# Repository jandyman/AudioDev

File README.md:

# AudioDev

Audio DSP development ecosystem for algorithm development, testing, and deployment.

## Active Projects

### [audio-graph-python](./audio-graph-python/)
Hybrid Faust/C++ audio processing graph system with Python control.
- Flat channel model (all signals mono, multichannel = N parallel signals)
- Uniform interface for Faust and C++ processors
- Named processor access, capture mode for debugging, chunked processing
- Graph specification language for cascade definitions

### [dsp_library](./dsp_library/)
Framework-agnostic C++ and Faust DSP implementations shared across platforms.
- **C++ Processors**: example_processor, split_chorus
- **Faust Modules**: gain, split_gain, dual_tap_delay (9th order Lagrange interpolation)
- Single source of truth: write DSP once, wrap for Python and Max

### [max_externals](./max_externals/)
Max/MSP external wrappers for DSP processors.
- **dual_tap_delay~**: Faust-based dual tap delay
- **split_chorus~**: C++ split chorus effect
- Thin wrappers that include DSP from dsp_library

## Reference Projects

### [Embedded DSP DevSystem](./Embedded%20DSP%20DevSystem/)
Conceptual framework for DSP algorithm development lifecycle (Python prototyping to embedded C++).
Contains design documents and architectural decisions.

### [DaisyExamples](./DaisyExamples/)
Examples for Electro-Smith Daisy embedded audio platform. 80+ DSP algorithm examples.

### [SciPy](./SciPy/)
Python-based signal processing algorithm development and analysis.

### [PitchShifter](./PitchShifter/)
Early-stage bass guitar pitch shifter concept.

## Architecture

```
AudioDev/
├── dsp_library/           # Core DSP implementations (C++ and Faust)
│   ├── cpp/               # Framework-agnostic C++ DSP
│   └── faust/             # Faust DSP modules
├── audio-graph-python/    # Python graph system + pybind11 bindings
│   ├── python/            # Graph system
│   ├── bindings/          # pybind11 wrappers for dsp_library
│   └── examples/          # Working examples
├── max_externals/         # Max/MSP external wrappers
│   ├── dual_tap_delay_tilde/
│   └── split_chorus_tilde/
└── ...                    # Reference projects
```

## Design Principles

1. **Single source of truth**: DSP code lives in `dsp_library/`, wrapped for each platform
2. **Flat channel model**: All signals are mono, multichannel is N parallel mono signals
3. **Uniform interface**: All processors expose `init/process/set_param/get_param`
4. **Framework-agnostic**: Core DSP has no dependencies on Max, Python, or any framework

## Getting Started

See [audio-graph-python/QUICKSTART.md](./audio-graph-python/QUICKSTART.md) for a 5-minute introduction.

## Recent Changes

See [audio-graph-python/CHANGELOG.md](./audio-graph-python/CHANGELOG.md) for recent updates.

**Latest (2026-01-15)**:
- Split chorus C++ module with Python bindings
- Graph specification language for cascade definitions
- File reorganization with dsp_library as central DSP source

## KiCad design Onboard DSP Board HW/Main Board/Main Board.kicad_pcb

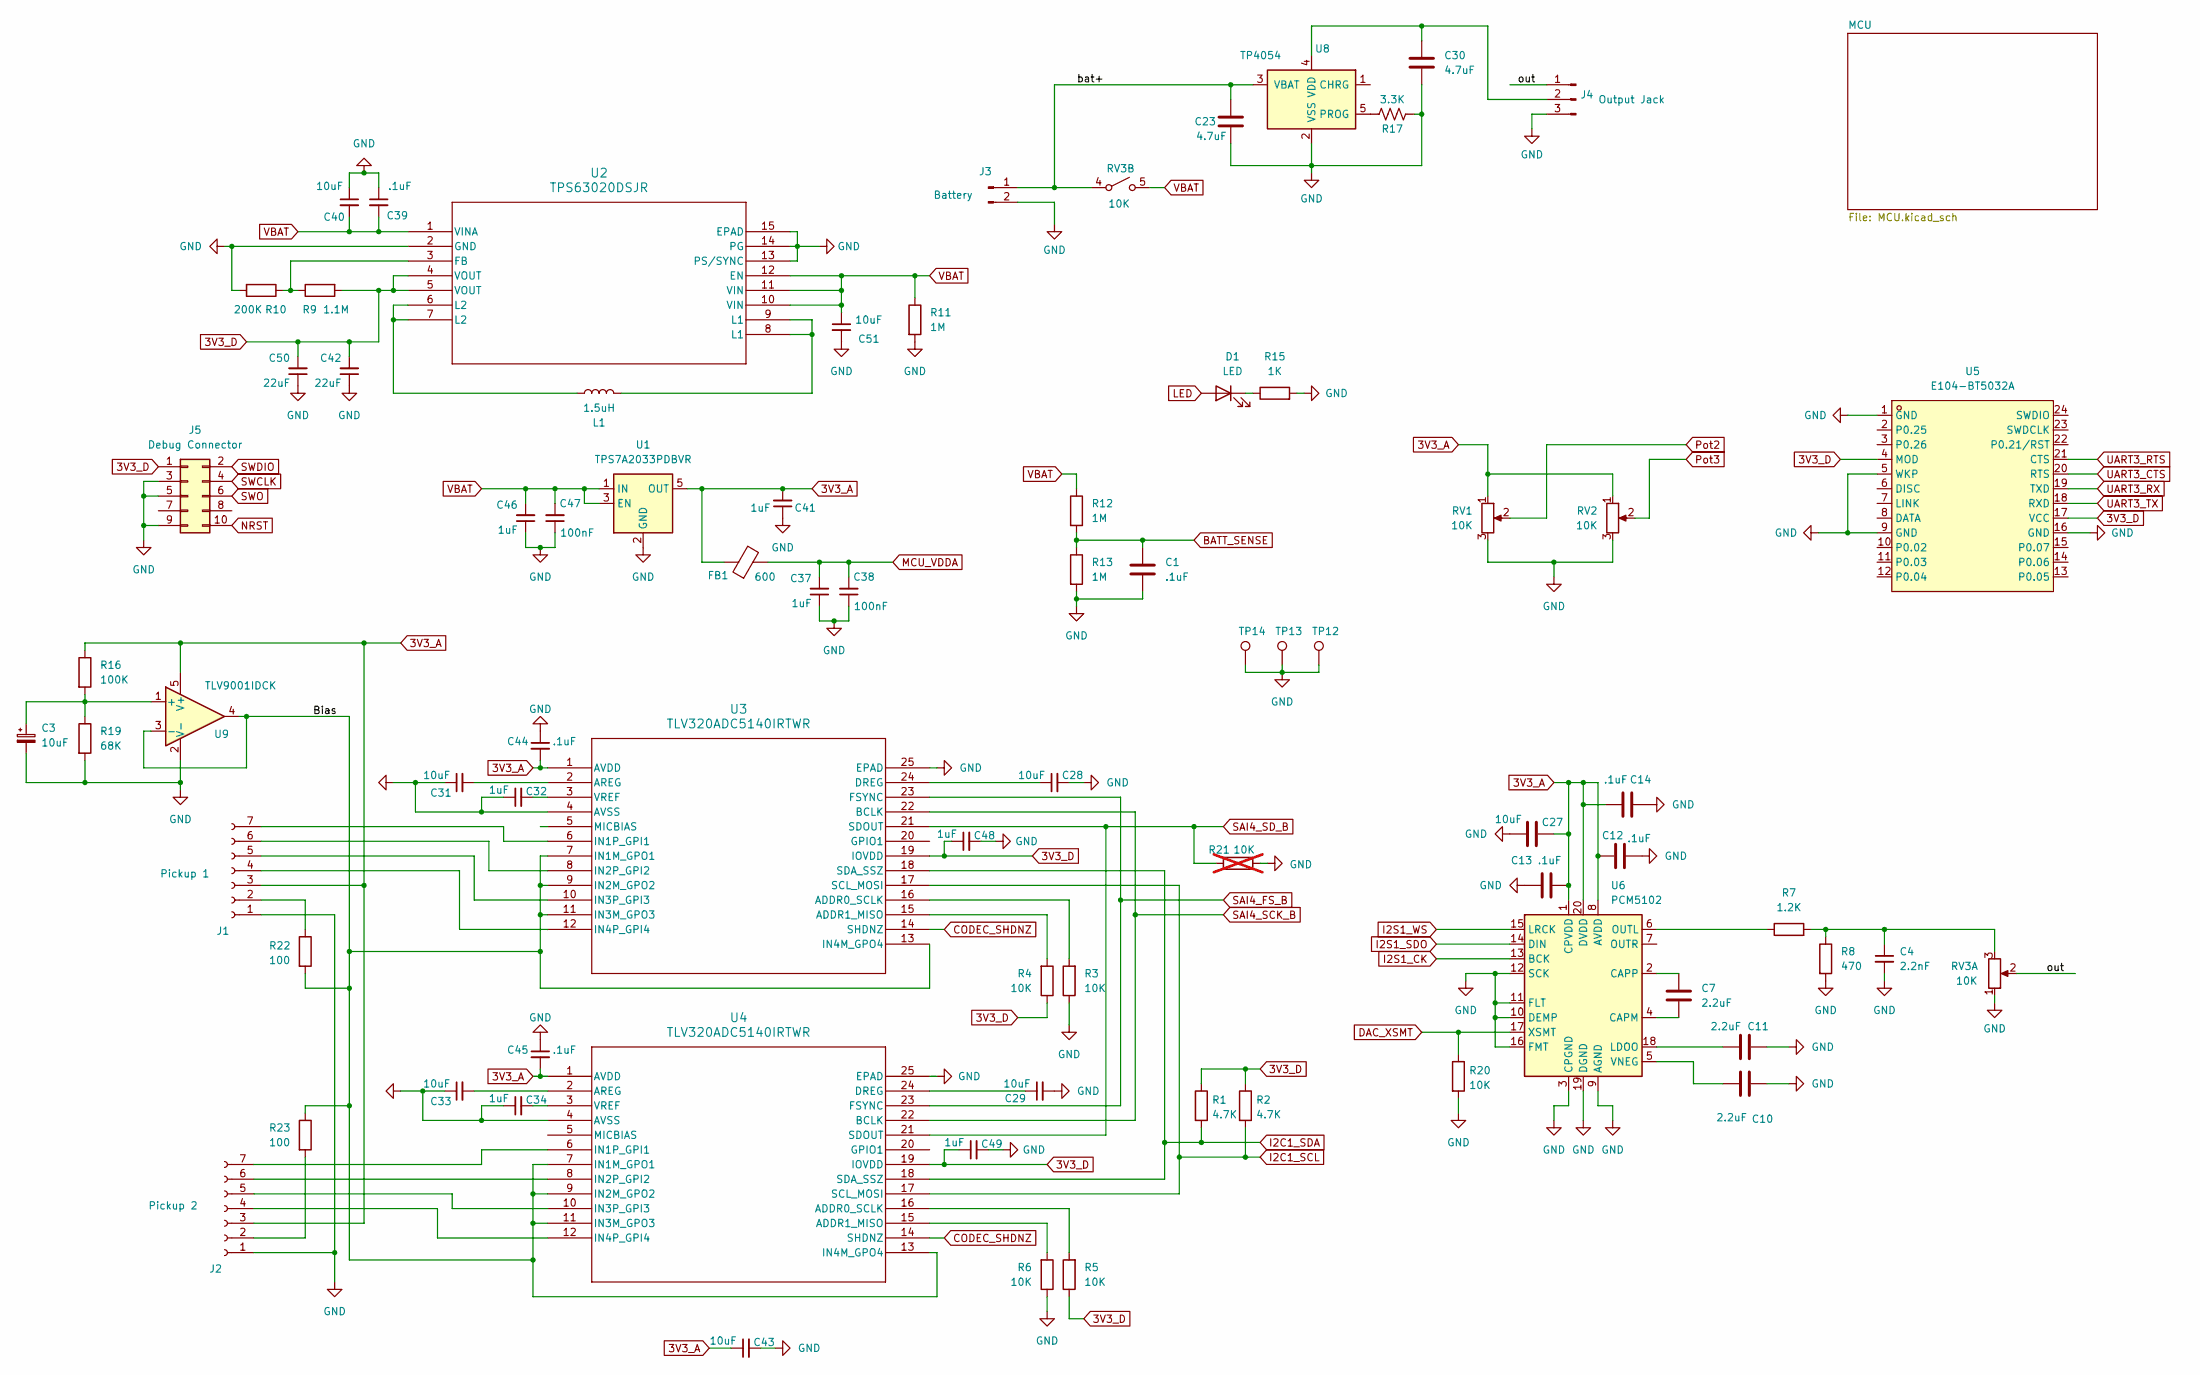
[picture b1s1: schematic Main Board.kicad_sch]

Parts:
C1, C12, C13, C14, C39, C44, C45: .1uF; C_0402_1005Metric
C3: 10uF; CP_EIA-3216-18_Kemet-A
C4: 2.2nF; C_0603_1608Metric
C7, C10, C11: 2.2uF; C_0402_1005Metric
C23, C30: 4.7uF; C_0402_1005Metric
C27, C40, C43, C51: 10uF; C_0805_2012Metric
C28, C29, C31, C33: 10uF; C_0402_1005Metric
C32, C34, C37, C41, C46, C48, C49: 1uF; C_0402_1005Metric
C38, C47: 100nF; C_0402_1005Metric
C42, C50: 22uF; C_0805_2012Metric
D1: LED; LED_0603_1608Metric
FB1: 600; L_0603_1608Metric
J1: Pickup 1; PinHeader_1x07_P2.00mm_Horizontal
J2: Pickup 2; PinHeader_1x07_P2.00mm_Horizontal
J3: Battery; JST_PH_S2B-PH-K_1x02_P2.00mm_Horizontal
J4: Output Jack; PinHeader_1x03_P2.54mm_Vertical
J5: Debug Connector; PinHeader_2x05_P1.27mm_Vertical
L1: 1.5uH; L_Sunlord_SWPA4030S
R1, R2: 4.7K; R_0402_1005Metric
R3, R4, R5, R6, R20: 10K; R_0402_1005Metric
R7: 1.2K; R_0402_1005Metric
R8: 470; R_0402_1005Metric
R9: 1.1M; R_0402_1005Metric
R10: 200K; R_0402_1005Metric
R11, R12, R13: 1M; R_0402_1005Metric
R15: 1K; R_0402_1005Metric
R16: 100K; R_0402_1005Metric
R17: 3.3K; R_0402_1005Metric
R19: 68K; R_0402_1005Metric
R21: 10K; R_0402_1005Metric; not fitted
R22, R23: 100; R_0402_1005Metric
RV1, RV2: 10K; Potentiometer_Alps_RK097_Single_Horizontal
RV3: 10K; Potentiometer_Chinese_Single_Horizontal_Switch
TP12, TP13, TP14: TestPoint_Plated_Hole_ID7_OD1.2mm
U1: TPS7A2033PDBVR; SOT-23-5
U2: TPS63020DSJR; DSJ14_2P85X1P58
U3, U4: TLV320ADC5140IRTWR; RTW24_4P15X4P15_TEX
U5: E104-BT5032A; WIRELM-SMD_E104-BT5010A; MPN E104-BT5032A
U6: PCM5102; TSSOP-20_4.4x6.5mm_P0.65mm
U8: TP4054; SOT-23-5
U9: TLV9001IDCK; SOT-353_SC-70-5

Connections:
3V3_A: C12.1, C13.2, C14.2, C27.1, C41.2, C43.1, C44.2, C45.2, FB1.1, J1.3, J2.3, R16.1, RV1.1, RV2.1, U1.5 (OUT), U3.1 (AVDD), U4.1 (AVDD), U6.1 (CPVDD), U6.8 (AVDD), U6.20 (DVDD), U9.5 (V+)
3V3_D: C42.2, C48.1, C49.1, C50.2, J5.1, R1.1, R2.1, R4.1, R5.1, R9.2, U2.4 (VOUT), U2.5 (VOUT), U3.19 (IOVDD), U4.19 (IOVDD), U5.4 (MOD), U5.17 (VCC); also elsewhere on the board
/Bias: R22.2, R23.1, U3.7 (IN1M_GPO1), U3.9 (IN2M_GPO2), U3.11 (IN3M_GPO3), U3.13 (IN4M_GPO4), U4.7 (IN1M_GPO1), U4.9 (IN2M_GPO2), U4.11 (IN3M_GPO3), U4.13 (IN4M_GPO4), U9.3 (-), U9.4
/bat+: C23.1, J3.1, RV3.4 (A), U8.3 (VBAT)
/out: J4.1, RV3.2
BATT_SENSE: C1.1, R12.2, R13.1; also elsewhere on the board
CODEC_SHDNZ: U3.14 (SHDNZ), U4.14 (SHDNZ); also elsewhere on the board
DAC_XSMT: R20.1, U6.17 (XSMT); also elsewhere on the board
GND: C1.2, C3.2, C4.2, C10.2, C11.2, C12.2, C13.1, C14.1, C23.2, C27.2, C28.2, C29.2, C30.2, C31.1, C32.1, C33.1, C34.1, C37.1, C38.1, C39.1, C40.1, C41.1, C42.1, C43.2, C44.1, C45.1, C46.1, C47.1, C48.2, C49.2, C50.1, C51.2, J1.1, J2.1, J3.2, J4.3, J5.3, J5.5, J5.9, R3.1, R6.1, R8.2, R10.2, R11.2, R13.2, R15.2, R17.1, R19.2, R20.2, R21.2, RV1.3, RV2.3, RV3.1, TP12.1 (1_1), TP13.1 (1_1), TP14.1 (1_1), U1.2 (GND), U2.2 (GND), U2.13 (PS/SYNC), U2.14 (PG), U2.15 (EPAD), U3.4 (AVSS), U3.25 (EPAD), U4.4 (AVSS), U4.25 (EPAD), U5.1 (GND), U5.5 (WKP), U5.9 (GND), U5.16 (GND), U6.3 (CPGND), U6.9 (AGND), U6.10 (DEMP), U6.11 (FLT), U6.12 (SCK), U6.16 (FMT), U6.19 (DGND), U8.2 (VSS), U9.2 (V-); also elsewhere on the board
I2C1_SCL: R2.2, U3.17 (SCL_MOSI), U4.17 (SCL_MOSI); also elsewhere on the board
I2C1_SDA: R1.2, U3.18 (SDA_SSZ), U4.18 (SDA_SSZ); also elsewhere on the board
I2S1_CK: U6.13 (BCK); also elsewhere on the board
I2S1_SDO: U6.14 (DIN); also elsewhere on the board
I2S1_WS: U6.15 (LRCK); also elsewhere on the board
LED: D1.2 (A); also elsewhere on the board
MCU_VDDA: C37.2, C38.2, FB1.2; also elsewhere on the board
NRST: J5.10; also elsewhere on the board
unnamed: C4.1, R7.2, R8.1, RV3.3
unnamed: D1.1 (K), R15.1
unnamed: J1.2, R22.1
unnamed: J1.4, U3.12 (IN4P_GPI4)
unnamed: J1.5, U3.10 (IN3P_GPI3)
unnamed: J1.6, U3.8 (IN2P_GPI2)
unnamed: J1.7, U3.6 (IN1P_GPI1)
unnamed: J2.2, R23.2
unnamed: J2.4, U4.12 (IN4P_GPI4)
unnamed: J2.5, U4.10 (IN3P_GPI3)
unnamed: J2.6, U4.8 (IN2P_GPI2)
unnamed: J2.7, U4.6 (IN1P_GPI1)
unnamed: C30.1, J4.2, U8.4 (VDD)
unnamed: L1.1, U2.8 (L1), U2.9 (L1)
unnamed: L1.2, U2.6 (L2), U2.7 (L2)
unnamed: R9.1, R10.1, U2.3 (FB)
unnamed: R3.2, U3.16 (ADDR0_SCLK)
unnamed: R4.2, U3.15 (ADDR1_MISO)
unnamed: C31.2, U3.2 (AREG)
unnamed: C28.1, U3.24 (DREG)
unnamed: C32.2, U3.3 (VREF)
unnamed: R5.2, U4.16 (ADDR0_SCLK)
unnamed: R6.2, U4.15 (ADDR1_MISO)
unnamed: C33.2, U4.2 (AREG)
unnamed: C29.1, U4.24 (DREG)
unnamed: C34.2, U4.3 (VREF)
unnamed: C7.2, U6.4 (CAPM)
unnamed: C7.1, U6.2 (CAPP)
unnamed: C11.1, U6.18 (LDOO)
unnamed: R7.1, U6.6 (OUTL)
unnamed: C10.1, U6.5 (VNEG)
unnamed: R17.2, U8.5 (PROG)
unnamed: C3.1, R16.2, R19.1, U9.1 (+)
Pot2: RV1.2; also elsewhere on the board
Pot3: RV2.2; also elsewhere on the board
SAI4_FS_B: U3.23 (FSYNC), U4.23 (FSYNC); also elsewhere on the board
SAI4_SCK_B: U3.22 (BCLK), U4.22 (BCLK); also elsewhere on the board
SAI4_SD_B: R21.1, U3.21 (SDOUT), U4.21 (SDOUT); also elsewhere on the board
SWCLK: J5.4; also elsewhere on the board
SWDIO: J5.2; also elsewhere on the board
SWO: J5.6; also elsewhere on the board
UART3_CTS: U5.20 (RTS); also elsewhere on the board
UART3_RTS: U5.21 (CTS); also elsewhere on the board
UART3_RX: U5.19 (TXD); also elsewhere on the board
UART3_TX: U5.18 (RXD); also elsewhere on the board
VBAT: C39.2, C40.2, C46.2, C47.2, C51.1, R11.1, R12.1, RV3.5 (B), U1.1 (IN), U1.3 (EN), U2.1 (VINA), U2.10 (VIN), U2.11 (VIN), U2.12 (EN)

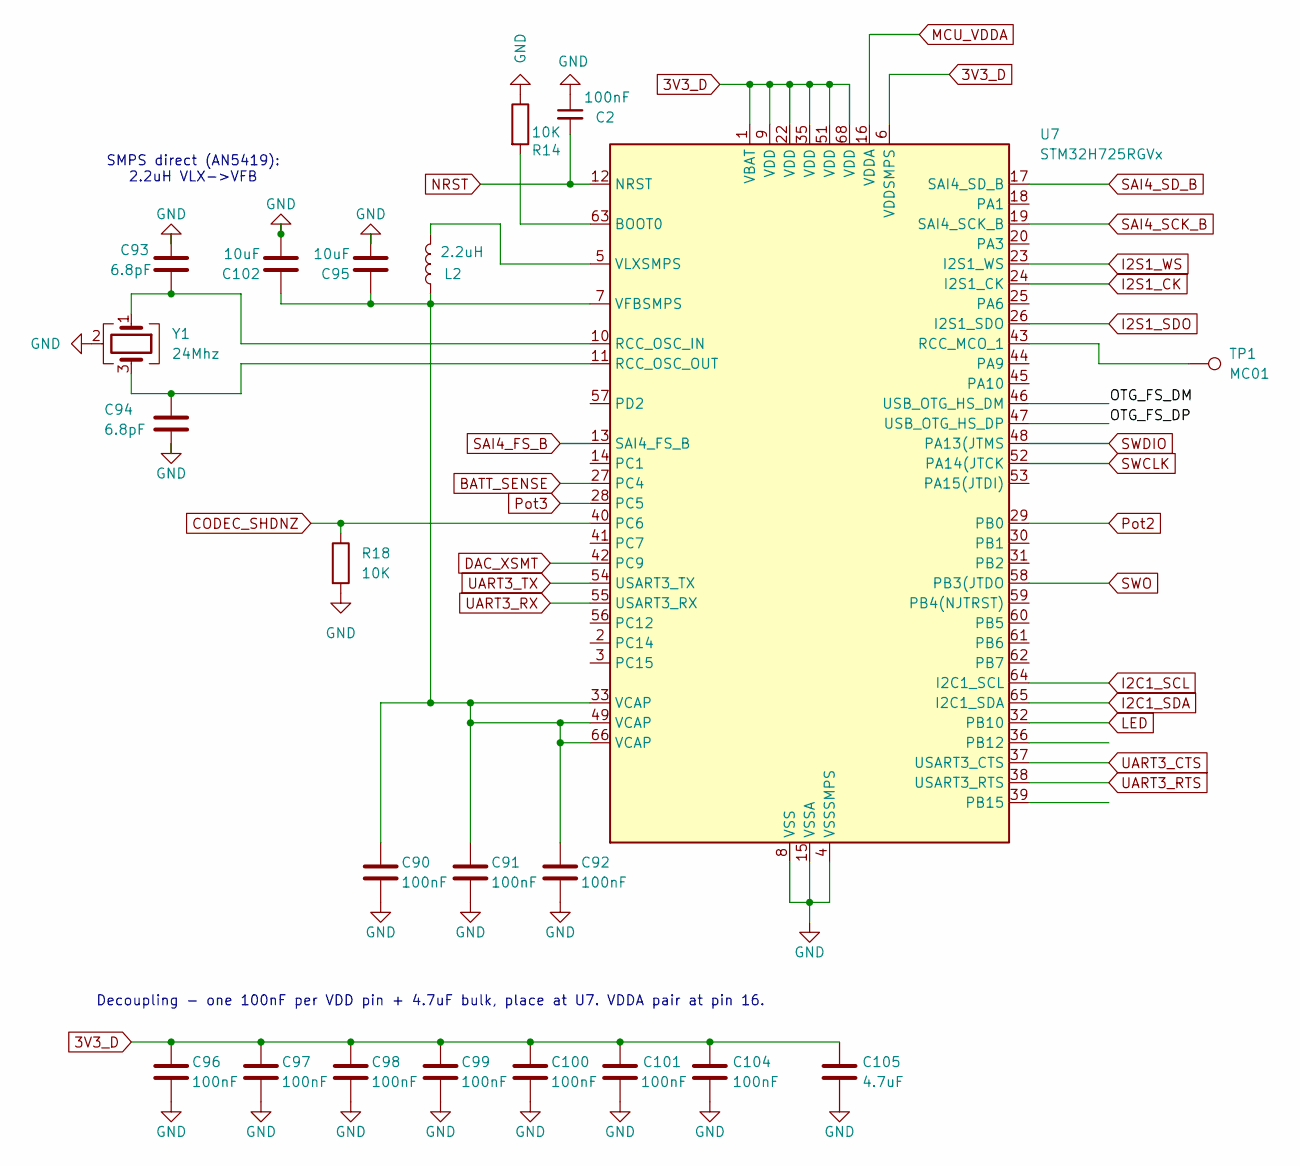
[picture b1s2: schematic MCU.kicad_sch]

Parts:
C2, C90, C91, C92, C96, C97, C98, C99, C100, C101, C104: 100nF; C_0402_1005Metric
C93, C94: 6.8pF; C_0402_1005Metric
C95, C102: 10uF; C_0603_1608Metric
C105: 4.7uF; C_0805_2012Metric
L2: 2.2uH; L_Sunlord_SWPA252012S
R14, R18: 10K; R_0402_1005Metric
TP1: MC01; TestPoint_Plated_Hole_ID4_OD7.0mm
U7: STM32H725RGVx; QFN-68-1EP_8x8mm_P0.4mm_EP6.4x6.4mm
Y1: 24Mhz; Crystal_SMD_WE_IQXC-26-4Pin_1.6x1.2mm

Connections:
3V3_D: C96.1, C97.1, C98.1, C99.1, C100.1, C101.1, C104.1, C105.1, U7.1 (VBAT), U7.6 (VDDSMPS), U7.9 (VDD), U7.22 (VDD), U7.35 (VDD), U7.51 (VDD), U7.68 (VDD); also elsewhere on the board
/MCU/OTG_FS_DM: U7.46 (USB_OTG_HS_DM)
/MCU/OTG_FS_DP: U7.47 (USB_OTG_HS_DP)
BATT_SENSE: U7.27 (PC4); also elsewhere on the board
CODEC_SHDNZ: R18.1, U7.40 (PC6); also elsewhere on the board
DAC_XSMT: U7.42 (PC9); also elsewhere on the board
GND: C2.1, C90.2, C91.2, C92.2, C93.2, C94.2, C95.2, C96.2, C97.2, C98.2, C99.2, C100.2, C101.2, C102.2, C104.2, C105.2, R14.1, R18.2, U7.4 (VSSSMPS), U7.8 (VSS), U7.15 (VSSA), U7.21 (VSS), U7.34 (VSS), U7.50 (VSS), U7.67 (VSS), U7.69 (VSS), Y1.2 (G), Y1.4 (G); also elsewhere on the board
I2C1_SCL: U7.64 (I2C1_SCL); also elsewhere on the board
I2C1_SDA: U7.65 (I2C1_SDA); also elsewhere on the board
I2S1_CK: U7.24 (I2S1_CK); also elsewhere on the board
I2S1_SDO: U7.26 (I2S1_SDO); also elsewhere on the board
I2S1_WS: U7.23 (I2S1_WS); also elsewhere on the board
LED: U7.32 (PB10); also elsewhere on the board
MCU_VDDA: U7.16 (VDDA); also elsewhere on the board
NRST: C2.2, U7.12 (NRST); also elsewhere on the board
unnamed: R14.2, U7.63 (BOOT0)
unnamed: TP1.1 (1_1), U7.43 (RCC_MCO_1)
unnamed: C93.1, U7.10 (RCC_OSC_IN), Y1.1
unnamed: C94.1, U7.11 (RCC_OSC_OUT), Y1.3
unnamed: C90.1, C91.1, C92.1, C95.1, C102.1, L2.1, U7.7 (VFBSMPS), U7.33 (VCAP), U7.49 (VCAP), U7.66 (VCAP)
unnamed: L2.2, U7.5 (VLXSMPS)
Pot2: U7.29 (PB0); also elsewhere on the board
Pot3: U7.28 (PC5); also elsewhere on the board
SAI4_FS_B: U7.13 (SAI4_FS_B); also elsewhere on the board
SAI4_SCK_B: U7.19 (SAI4_SCK_B); also elsewhere on the board
SAI4_SD_B: U7.17 (SAI4_SD_B); also elsewhere on the board
SWCLK: U7.52 (PA14(JTCK); also elsewhere on the board
SWDIO: U7.48 (PA13(JTMS); also elsewhere on the board
SWO: U7.58 (PB3(JTDO); also elsewhere on the board
UART3_CTS: U7.37 (USART3_CTS); also elsewhere on the board
UART3_RTS: U7.38 (USART3_RTS); also elsewhere on the board
UART3_RX: U7.55 (USART3_RX); also elsewhere on the board
UART3_TX: U7.54 (USART3_TX); also elsewhere on the board

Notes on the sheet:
SMPS direct (AN5419): 2.2uH VLX->VFB
Decoupling - one 100nF per VDD pin + 4.7uF bulk, place at U7. VDDA pair at pin 16.

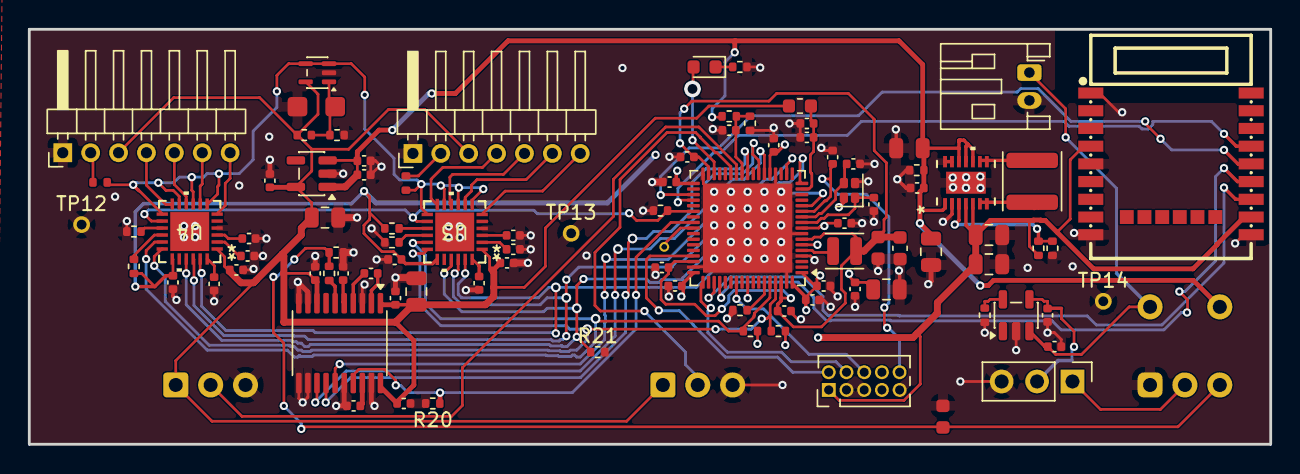
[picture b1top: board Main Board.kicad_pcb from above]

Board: 4 copper layers, 89.0 x 29.8 mm, 98 parts (0 on the bottom side), 69 nets.

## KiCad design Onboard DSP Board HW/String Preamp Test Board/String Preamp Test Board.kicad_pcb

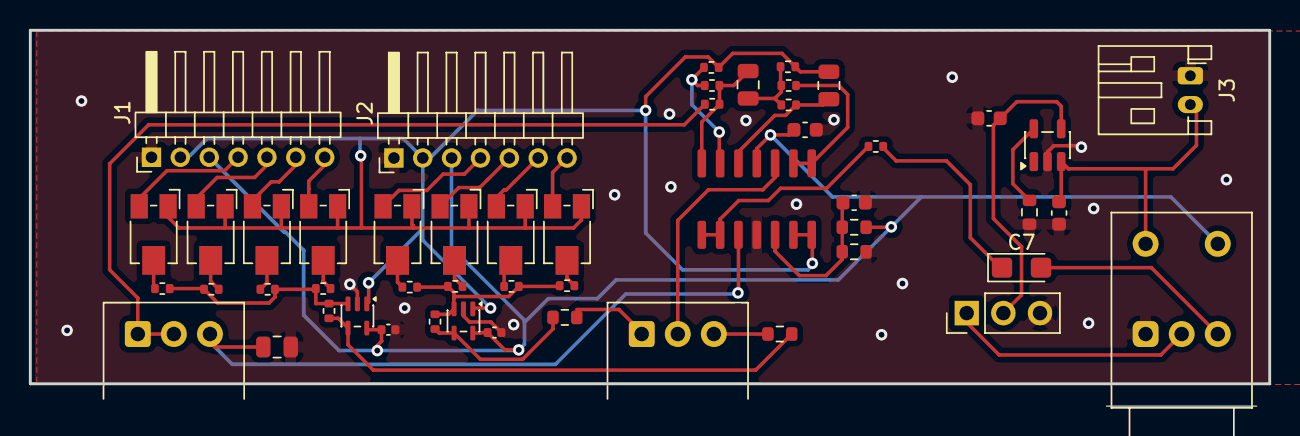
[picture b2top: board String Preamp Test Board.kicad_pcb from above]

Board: 2 copper layers, 85.9 x 26.0 mm, 51 parts (0 on the bottom side), 41 nets.

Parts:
C2, C3, C6: 5.6nF; C_0805_2012Metric
C7: 4.7uF; CP_EIA-3216-10_Kemet-I
C9, C11: 100nF; C_0402_1005Metric
C12, C15: 4.7uF; C_0603_1608Metric
C13, C14: 100nF; C_0603_1608Metric
J1, J2: Conn_01x07_Socket; PinHeader_1x07_P2.00mm_Horizontal
J3: Battery; JST_PH_S2B-PH-K_1x02_P2.00mm_Horizontal
J4: Output Jack; PinHeader_1x03_P2.54mm_Vertical
R1, R2: 22k; R_0603_1608Metric
R3, R6: 15K; R_0402_1005Metric
R4: 6.2K; R_0402_1005Metric
R5, R14: 10K; R_0402_1005Metric
R9: 100; R_0402_1005Metric
R10, R11, R12, R13, R16, R17, R18, R19, R20, R23: 20k; R_0402_1005Metric
R15: 2.2k; R_0402_1005Metric
R24, R25: 10k; R_0603_1608Metric
R26: 30k; R_0603_1608Metric
RV1: 100k; Potentiometer_Alps_RK097_Single_Horizontal
RV2: A100K; Potentiometer_Alps_RK097_Single_Horizontal
RV3: 10K; Potentiometer_Alps_RK097_Single_Horizontal_Switch
RV4, RV5, RV6, RV7, RV8, RV9, RV10, RV11: 10k; Potentiometer_Bourns_TC33X_Vertical_HandSolder
U1: TLV9004; SOIC-14_3.9x8.7mm_P1.27mm
U2, U3: TLV9001IDCK; SOT-353_SC-70-5
U5: TP4054; SOT-23-5

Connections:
/RV3_in: C7.2, RV3.3
/Summer1/sim_in: R17.1, RV8.2
/Summer/sim_in: R10.1, RV4.2
/VG: C3.2, J1.2, J2.2, R5.1, R14.1, RV4.1, RV5.1, RV6.1, RV7.1, RV8.1, RV9.1, RV10.1, RV11.1, U1.13 (-), U1.14, U2.1 (+), U3.1 (+)
/bat+: C12.1, J3.2, RV3.4 (A), U5.3 (VBAT)
/buf_in: C6.2, RV2.3, U1.10 (+)
/filt_out: R15.2, RV2.1, RV2.2
/out: J4.1, RV3.2
/p1_out: R1.2, R16.2, U2.4
/p2_out: R2.1, R23.2, U3.4
/sum_in: RV1.2, U1.3 (+)
/sum_out: R3.1, U1.1, U1.2 (-)
/v+: C9.2, C11.2, C14.2, J1.3, J2.3, R24.2, RV3.5 (B), U1.4 (V+), U2.5 (V+), U3.5 (V+)
GND: C6.1, C9.1, C11.1, C12.2, C13.1, C14.1, C15.2, J1.1, J2.1, J3.1, J4.3, R25.1, R26.1, RV3.1, U1.11 (V-), U2.2 (V-), U3.2 (V-), U5.2 (VSS)
unnamed: C2.1, R3.2, R4.1, R14.2
unnamed: C2.2, R6.2, R15.1, U1.7
unnamed: C7.1, R9.2
unnamed: J1.4, RV7.3
unnamed: J1.5, RV6.3
unnamed: J1.6, RV5.3
unnamed: J1.7, RV4.3
unnamed: J2.4, RV11.3
unnamed: J2.5, RV10.3
unnamed: J2.6, RV9.3
unnamed: J2.7, RV8.3
unnamed: C15.1, J4.2, U5.4 (VDD)
unnamed: R1.1, RV1.3
unnamed: R2.2, RV1.1
unnamed: R11.1, RV5.2
unnamed: R12.1, RV6.2
unnamed: R13.1, RV7.2
unnamed: R18.1, RV9.2
unnamed: R19.1, RV10.2
unnamed: R20.1, RV11.2
unnamed: C3.1, R4.2, U1.5 (+)
unnamed: R5.2, R6.1, U1.6 (-)
unnamed: R9.1, U1.8, U1.9 (-)
unnamed: C13.2, R24.1, R25.2, U1.12 (+)
unnamed: R10.2, R11.2, R12.2, R13.2, R16.1, U2.3 (-)
unnamed: R17.2, R18.2, R19.2, R20.2, R23.1, U3.3 (-)
unnamed: R26.2, U5.5 (PROG)

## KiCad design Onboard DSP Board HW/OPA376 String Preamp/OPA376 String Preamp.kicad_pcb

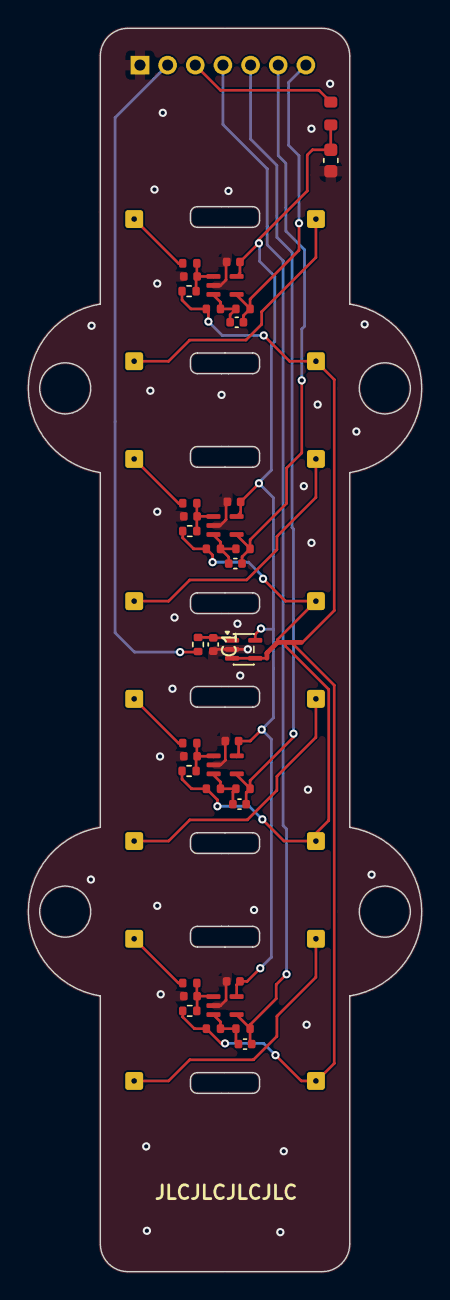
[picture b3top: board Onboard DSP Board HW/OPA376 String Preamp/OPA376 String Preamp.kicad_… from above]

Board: 2 copper layers, 28.4 x 89.9 mm, 54 parts (1 on the bottom side), 26 nets.

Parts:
C1, C10, C12, C14, C16: 100pF; C_0402_1005Metric
C3: 100nF; C_0603_1608Metric
C11, C13, C15, C21: 220pF; C_0402_1005Metric
C17, C18, C19, C20: 100nF; C_0402_1005Metric
J1, J5, J10, J14: Input; Magnet Wire THT
J2, J3, J4, J6, J7, J8, J11, J12, J13, J15, J16, J17: Magnet Wire THT
J18: PinHeader_1x07_P2.00mm_Horizontal
R2, R13, R16, R19, R22: 1K; R_0402_1005Metric
R3: 47; R_0603_1608Metric
R14, R17, R20, R23: 2.2K; R_0402_1005Metric
R15, R18, R21, R24: 15K; R_0402_1005Metric
R25, R26, R27, R28: 27K; R_0402_1005Metric
U1, U2, U3, U4, U5: OPA376AIDCKR; SOT-353_SC-70-5

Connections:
/3V3: J18.3, R3.1
/Bias: J18.2, R2.1
/SIngle FET preamp1/Output: C13.1, J18.6, R18.2, U2.4
/SIngle FET preamp1/in: J5.1 (Pin_1_1), R16.1
/SIngle FET preamp2/Output: C15.1, J18.5, R21.2, U3.4
/SIngle FET preamp2/in: J10.1 (Pin_1_1), R19.1
/SIngle FET preamp3/Output: C21.1, J18.4, R24.2, U4.4
/SIngle FET preamp3/in: J14.1 (Pin_1_1), R22.1
/SIngle FET preamp/3.3V: C3.1, C17.1, C18.1, C19.1, C20.1, R3.2, U1.5 (V+), U2.5 (V+), U3.5 (V+), U4.5 (V+), U5.5 (V+)
/SIngle FET preamp/MidRail: J2.1 (Pin_1_1), J8.1 (Pin_1_1), J13.1 (Pin_1_1), J17.1 (Pin_1_1), R14.1, R17.1, R20.1, R23.1, R25.1, R26.1, R27.1, R28.1, U5.3 (-), U5.4
/SIngle FET preamp/Output: C11.1, J18.7, R15.2, U1.4
/SIngle FET preamp/in: J1.1 (Pin_1_1), R13.1
GND: C1.2, C3.2, C10.1, C12.1, C14.1, C16.1, C17.2, C18.2, C19.2, C20.2, J18.1, U1.2 (V-), U2.2 (V-), U3.2 (V-), U4.2 (V-), U5.2 (V-)
unnamed: J3.1 (Pin_1_1), J4.1 (Pin_1_1)
unnamed: J6.1 (Pin_1_1), J7.1 (Pin_1_1)
unnamed: J11.1 (Pin_1_1), J12.1 (Pin_1_1)
unnamed: J15.1 (Pin_1_1), J16.1 (Pin_1_1)
unnamed: C10.2, R13.2, R25.2, U1.1 (+)
unnamed: C11.2, R14.2, R15.1, U1.3 (-)
unnamed: C12.2, R16.2, R26.2, U2.1 (+)
unnamed: C13.2, R17.2, R18.1, U2.3 (-)
unnamed: C14.2, R19.2, R27.2, U3.1 (+)
unnamed: C15.2, R20.2, R21.1, U3.3 (-)
unnamed: C16.2, R22.2, R28.2, U4.1 (+)
unnamed: C21.2, R23.2, R24.1, U4.3 (-)
unnamed: C1.1, R2.2, U5.1 (+)

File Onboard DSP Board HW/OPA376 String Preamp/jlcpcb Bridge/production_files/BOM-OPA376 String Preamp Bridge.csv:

Comment,Designator,Footprint,LCSC,Quantity
100K,R1,R_0402_1005Metric,C25741,1
100nF,"C17,C18,C19,C20",C_0402_1005Metric,C307331,4
100pF,"C10,C12,C14,C16",C_0402_1005Metric,C1546,4
10uF,C2,C_0603_1608Metric,C96446,1
15K,"R15,R18,R21,R24",R_0402_1005Metric,C25756,4
1K,"R13,R16,R19,R22",R_0402_1005Metric,C11702,4
2.2K,"R14,R17,R20,R23",R_0402_1005Metric,C25879,4
22uF,"C1,C11,C13,C15",C_0603_1608Metric,C59461,4
43K,R2,R_0402_1005Metric,C8329,1
OPA376,"U1,U2,U3,U4",SOT-353_SC-70-5,C42134,4

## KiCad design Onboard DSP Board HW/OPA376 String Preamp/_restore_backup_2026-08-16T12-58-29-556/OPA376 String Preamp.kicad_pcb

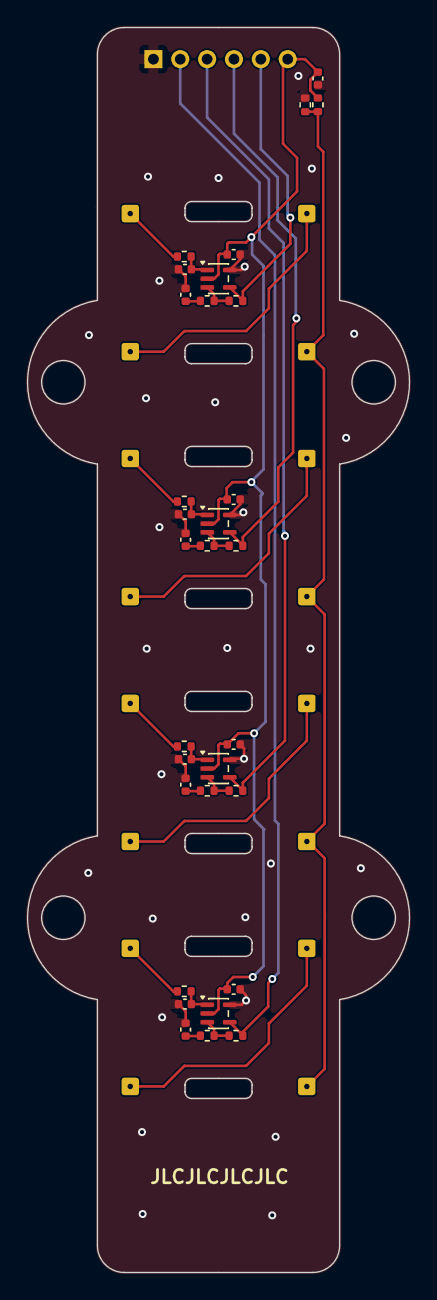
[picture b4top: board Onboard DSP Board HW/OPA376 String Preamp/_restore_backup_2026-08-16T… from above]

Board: 2 copper layers, 28.4 x 92.7 mm, 48 parts (1 on the bottom side), 27 nets.

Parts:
C1, C11, C13, C15: 22uF; C_0402_1005Metric
C2: C; C_0402_1005Metric
C10, C12, C14, C16: 100pF; C_0402_1005Metric
C17, C18, C19, C20: 100nF; C_0402_1005Metric
J1, J5, J10, J14: Input; Magnet Wire THT
J2, J3, J4, J6, J7, J8, J11, J12, J13, J15, J16, J17: Magnet Wire THT
J9: PinHeader_1x06_P2.00mm_Horizontal
R1, R2: R; R_0402_1005Metric
R13, R16, R19, R22: 1K; R_0402_1005Metric
R14, R17, R20, R23: 2.2K; R_0402_1005Metric
R15, R18, R21, R24: 15K; R_0402_1005Metric
U1, U2, U3, U4: TLV9001IDCK; SOT-353_SC-70-5

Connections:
/SIngle FET preamp1/Output: J9.4, R18.2, U2.4
/SIngle FET preamp2/Output: J9.3, R21.2, U3.4
/SIngle FET preamp3/Output: J9.2, R24.2, U4.4
/SIngle FET preamp/3.3V: C2.1, C17.1, C18.1, C19.1, C20.1, J9.6, R1.1, U1.2 (V-), U2.2 (V-), U3.2 (V-), U4.2 (V-)
/SIngle FET preamp/MidRail: J2.1 (Pin_1_1), J8.1 (Pin_1_1), J13.1 (Pin_1_1), J17.1 (Pin_1_1), R1.2, R2.1
/SIngle FET preamp/Output: J9.5, R15.2, U1.4
GND: C1.1, C2.2, C10.1, C11.1, C12.1, C13.1, C14.1, C15.1, C16.1, C17.2, C18.2, C19.2, C20.2, J9.1, R2.2, U1.5 (V+), U2.5 (V+), U3.5 (V+), U4.5 (V+)
unnamed: C1.2, R14.1
unnamed: C11.2, R17.1
unnamed: C13.2, R20.1
unnamed: C15.2, R23.1
unnamed: J1.1 (Pin_1_1), R13.1
unnamed: J3.1 (Pin_1_1), J4.1 (Pin_1_1)
unnamed: J5.1 (Pin_1_1), R16.1
unnamed: J6.1 (Pin_1_1), J7.1 (Pin_1_1)
unnamed: J10.1 (Pin_1_1), R19.1
unnamed: J11.1 (Pin_1_1), J12.1 (Pin_1_1)
unnamed: J14.1 (Pin_1_1), R22.1
unnamed: J15.1 (Pin_1_1), J16.1 (Pin_1_1)
unnamed: C10.2, R13.2, U1.1 (+)
unnamed: R14.2, R15.1, U1.3 (-)
unnamed: C12.2, R16.2, U2.1 (+)
unnamed: R17.2, R18.1, U2.3 (-)
unnamed: C14.2, R19.2, U3.1 (+)
unnamed: R20.2, R21.1, U3.3 (-)
unnamed: C16.2, R22.2, U4.1 (+)
unnamed: R23.2, R24.1, U4.3 (-)

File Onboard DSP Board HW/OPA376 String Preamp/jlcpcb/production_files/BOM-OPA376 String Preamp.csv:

Comment,Designator,Footprint,LCSC,Quantity
100pF,C16,C_0402_1005Metric,,1
100nF,C20,C_0402_1005Metric,,1
R,R2,R_0402_1005Metric,,1
1K,R22,R_0402_1005Metric,,1
15K,R18,R_0402_1005Metric,,1
100nF,C19,C_0402_1005Metric,,1
22uF,C11,C_0402_1005Metric,,1
15K,R15,R_0402_1005Metric,,1
100pF,C14,C_0402_1005Metric,,1
22uF,C13,C_0402_1005Metric,,1
1K,R16,R_0402_1005Metric,,1
2.2K,R14,R_0402_1005Metric,,1
1K,R13,R_0402_1005Metric,,1
15K,R24,R_0402_1005Metric,,1
OPA376,U4,SOT-353_SC-70-5,,1
22uF,C1,C_0402_1005Metric,,1
R,R1,R_0402_1005Metric,,1
2.2K,R20,R_0402_1005Metric,,1
100pF,C12,C_0402_1005Metric,,1
22uF,C15,C_0402_1005Metric,,1
OPA376,U3,SOT-353_SC-70-5,,1
2.2K,R17,R_0402_1005Metric,,1
100pF,C10,C_0402_1005Metric,,1
100nF,C17,C_0402_1005Metric,,1
C,C2,C_0402_1005Metric,,1
15K,R21,R_0402_1005Metric,,1
1K,R19,R_0402_1005Metric,,1
OPA376,U2,SOT-353_SC-70-5,,1
OPA376,U1,SOT-353_SC-70-5,,1
2.2K,R23,R_0402_1005Metric,,1
100nF,C18,C_0402_1005Metric,,1

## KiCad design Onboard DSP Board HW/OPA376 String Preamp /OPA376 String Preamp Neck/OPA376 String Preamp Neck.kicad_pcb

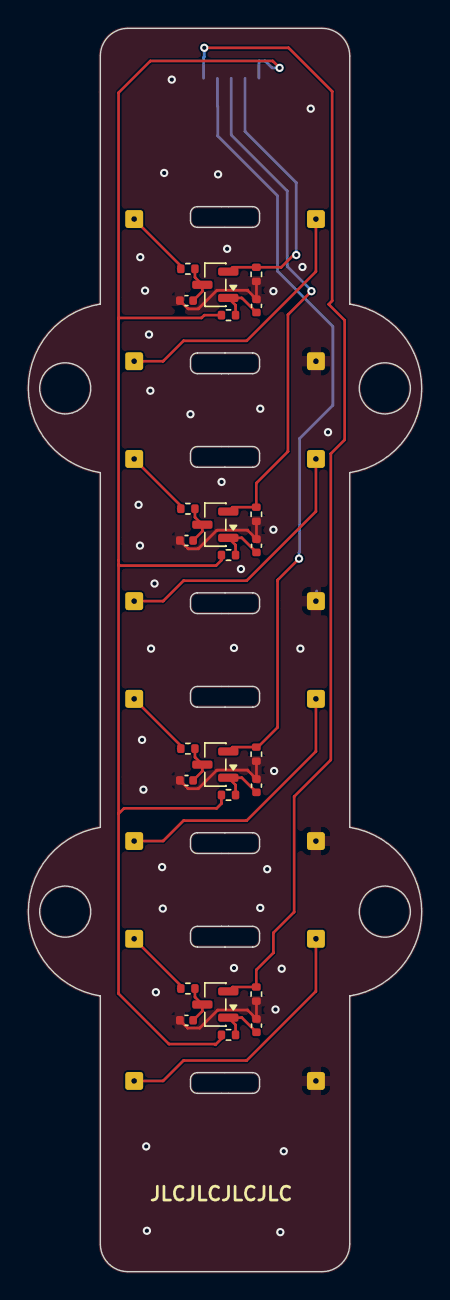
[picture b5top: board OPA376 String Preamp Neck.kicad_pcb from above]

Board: 2 copper layers, 28.4 x 89.9 mm, 41 parts (1 on the bottom side), 22 nets.

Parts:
C2, C5, C7, C9: 100nF; C_0402_1005Metric
C3, C4, C6, C8: 100pF; C_0402_1005Metric
J1, J5, J10, J14: Input; Magnet Wire THT
J2, J3, J4, J6, J7, J8, J11, J12, J13, J15, J16, J17: Magnet Wire THT
J9: JST_SH_SM06B-SRSS-TB_1x06-1MP_P1.00mm_Horizontal
Q1, Q2, Q3, Q4: MMBFJ201; SOT-23
R1, R4, R9, R12: 2.2K; R_0402_1005Metric
R2, R3, R7, R10: 1K; R_0402_1005Metric
R5, R6, R8, R11: 100; R_0402_1005Metric

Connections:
/SIngle FET preamp1/Output: J9.3, Q2.2 (S), R4.1
/SIngle FET preamp2/Output: J9.4, Q3.2 (S), R9.1
/SIngle FET preamp3/Output: J9.5, Q4.2 (S), R12.1
/SIngle FET preamp/3.7V: J9.1, R5.1, R6.1, R8.1, R11.1
/SIngle FET preamp/Output: J9.2, Q1.2 (S), R1.1
GND: C2.1, C3.1, C4.1, C5.1, C6.1, C7.1, C8.1, C9.1, J2.1 (Pin_1_1), J8.1 (Pin_1_1), J9.6, J13.1 (Pin_1_1), J17.1 (Pin_1_1), R1.2, R4.2, R9.2, R12.2
unnamed: J1.1 (Pin_1_1), R2.1
unnamed: J3.1 (Pin_1_1), J4.1 (Pin_1_1)
unnamed: J5.1 (Pin_1_1), R3.1
unnamed: J6.1 (Pin_1_1), J7.1 (Pin_1_1)
unnamed: J10.1 (Pin_1_1), R7.1
unnamed: J11.1 (Pin_1_1), J12.1 (Pin_1_1)
unnamed: J14.1 (Pin_1_1), R10.1
unnamed: J15.1 (Pin_1_1), J16.1 (Pin_1_1)
unnamed: C2.2, Q1.1 (D), R5.2
unnamed: C3.2, Q1.3 (G), R2.2
unnamed: C5.2, Q2.1 (D), R6.2
unnamed: C4.2, Q2.3 (G), R3.2
unnamed: C7.2, Q3.1 (D), R8.2
unnamed: C6.2, Q3.3 (G), R7.2
unnamed: C9.2, Q4.1 (D), R11.2
unnamed: C8.2, Q4.3 (G), R10.2

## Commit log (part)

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2019-04-14 nested view controller setup seems to work
2019-04-15 making progress. End of stage one is now in sight
2019-04-15 parameter UI is functioning correctly using internal state of C++ DSP
2019-04-17 move the frequency analysis to C++, code complete no debug. Not hooked up to UI yet.
2019-04-17 UI almost finished, just need C++ to Swift data conversion
2019-04-25 EQ Display working with UI. Haven't tried live audio yet
2019-04-26 UI improvements
2019-04-28 solve a thread safety problem
2019-04-28 get CoreDspTest working with modified code
2019-04-29 fix hi shelf 6
2019-04-29 new thread safety mechanism works, non realtime too
2019-05-03 reduce latency. Ready for Dave review
2019-05-04 add mixer and joiner, fix nullsrc
2019-05-11 Reorg, add level meter page
2019-05-19 app seems to be in good shape for this rev.
2019-05-23 WIP including some JSON
2019-05-28 eliminate using statements at namespace level in hpp files
2019-05-29 WIP on JSon
2019-05-30 save and restore of basic config works
2019-05-30 Make the repo standalone, by including CorePlot
2019-05-30 WIP on adding relative gain, master gain, and in/out phase switch
2019-05-30 Update JSON
2019-06-01 work on labeled switch mute button
2019-06-05 This stage of the app seems to work. Includes a mixer section and save and restore of working copy
2019-06-23 add bass clef icon to project
2019-06-25 Get rid of UIStackViews
2019-07-09 Wire program now works well with Behringer 4 channel interface
2019-07-10 4 channel wire demo working WITH audio unit!
2019-07-10 add missing file, plus audio unit with dynamic bus size now works!
2019-07-26 before moving to Swift 5
2019-08-01 Add route change handling and clean up AudioPath object. Untested
2019-08-22 Works with Behringer, supports live connect and disconnect. But needs some state machine cleanup
2019-08-24 storyboard cleanup
2019-09-06 minor bug fix
2019-11-02 refactor to retain design level info. Connect and Describe work now. FlattenDestinationNets is crashing.
2020-01-22 try converting to just PinSpecs during first phase of graph, until we flatten the heirarchy. Compiles, but probably doesn't work.
2020-01-24 WIP on major refactor, moving design operation order
2020-01-31 WIP, getting close to completing big refactor
2020-02-01 Getting closer, basic graph contstruction now works
2020-02-02 Everything through determining processing order works now
2020-02-02 Don't save DerivedData
2020-02-03 UpdateWireSpecs works now. Next step - create function for allocating buffers
2020-02-04 Minor refactor
2020-02-15 Everything seems to look right but we get no output.
2020-02-17 We now have output. Further analysis required
2020-02-26 WIP, starting to integrate Python interop
2020-02-27 WIP. Got an example of coefgen interop working
2020-02-27 Interop with coef generation is working!
2020-03-03 Start working with Catalyst. Discover issues. Test SimpleEq graph with CoreDspTest, leading to discovery of bugs in refactor
2020-04-17 WIP. Pickup analyzer, work with pybind11
2020-04-26 WIP reorg to support python interop and testing
2020-04-27 working pybind11 test of a DSP block!
2020-04-30 significant progress on unit testing DSP blocks
2020-05-01 updated fddlconvolver compiles, wrapper for Python test almost done
2020-05-09 Got cmake to create xcode projects successfully. Templatized the block_test function, prepare to test convolver
2020-05-27 ready for retest of FddlConvolver, attach to process debugging now working
2020-10-18 Updates pickup analyzer, plus start new version of genericDSP oriented toward Python design time tools
2020-10-24 progress on Python GenericDSP
2025-12-22 Large commit
2026-01-07 move max-sdk
2026-01-07 test commit
2026-01-15 File reorganization, Faust split chorus
2026-01-16 fix layout of chorus_faust
2026-04-16 Add CubeIDE Makefile project for seed_h750
    Wires up STM32CubeIDE as a debug/browse/build frontend for the
    hand-written Makefile project. Built via the CubeIDE wizard
    (Makefile project type, no managed build, no HAL), then hand-tuned:
    - target_mcu set to STM32H750IBKx (UFBGA176+25, the package on
    Daisy Seed Rev 7) so the SFR view binds to the right device.
    - language.settings.xml populated with workspace-relative include
2026-04-16 Add coding standards and rework seed_h750 sources to comply
    Coding standards (docs/coding_standards.md):
    - Base style: 1TBS — opening brace on same line for everything
    (functions, structs, classes, enums, control blocks).
    - Indent: 2 spaces, no hard tabs.
    - snake_case throughout; established acronyms (dma, sai, pll, ...)
    stay as acronyms.
2026-05-10 Get several projects up to date
2026-05-12 Ignore Python __pycache__/ and *.pyc
2026-05-13 WIP on param_walker
2026-05-31 Pitch shifter: 3-tap delay + level-based attack detector + hold_env
    Three-tap delay port (dual_tap_delay → triple_tap_delay, mixer2 → mixer3):
    the loop_controller now manages 3 taps with role indices (active /
    loop_incoming / attack) floating across {0,1,2}, and a mode machine
    (LOOP_ONLY / ATTACK_FADEIN / ATTACK_FADEOUT) for the attack response.
    Attack tap engages with MIN_DELAY, fades in over 1ms, then loop pair
    fades out over 10ms (new ATTACK_FADEOUT_MS) before the attack tap
2026-06-30 feat(pitch_shifter): output_splicer — attack/note-end dry-wet crossfade
    New stateful block on the output: out = dry*m + wet*(1-m), where
    m = max(e_attack, e_noteend). An attack edge snaps dry live (1 ms rise) then
    crossfades back to wet over attack_to_wet_ms; dive_strength fades dry up over
    note_end_fade_ms as a note ends. Sharpens the attack transient (it does NOT
    mask YIN/loop latency — the shifted note is audible underneath a long
    crossfade). Both times are runtime params; dry_mix exposed as a probe.
2026-06-30 fix(pitch_shifter): kill low-note gain modulation — latched note-end + period-mean gate
    Two independent ripple bugs, both rooted in dive_strength/active_gain rippling
    at the note fundamental on low notes (detector RMS window < one period):
    - output_splicer: note-end was a continuous follower of dive_strength, so its
    ripple bled into dry_mix mid-note. Replaced with a latched one-shot — dive
    crossing NOTE_END_THRESH (0.5) latches dry, held until the next attack clears
    it (attack hands the dry level to e_attack, so the crossfade back to wet is
